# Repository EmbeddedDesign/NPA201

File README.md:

# NPA201
Amphenol NPA 201 library

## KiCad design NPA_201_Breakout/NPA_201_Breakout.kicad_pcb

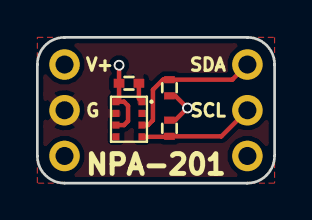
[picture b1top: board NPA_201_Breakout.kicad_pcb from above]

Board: 2 copper layers, 13.2 x 8.1 mm, 6 parts (0 on the bottom side), 4 nets.

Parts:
C1: 0.1uF; C_0402
P1: PWR_CONN; Pin_Header_1x3_2.54mm_Pitch
P2: I2C_CONN; Pin_Header_1x3_2.54mm_Pitch
R1, R2: 4.7K; R_0402
U1: NPA201; NPA_201

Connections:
+3V3: C1.1, P1.1, R1.1, R2.1, U1.6, U1.8
/I2C_SCL: P2.2, R1.2, U1.4
/I2C_SDA: P2.1, R2.2, U1.3
GND: C1.2, P1.2, U1.1, U1.7

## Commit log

2017-01-26 Add NPA 201 breakout board
2017-01-31 don't relase bus after ending transmission
